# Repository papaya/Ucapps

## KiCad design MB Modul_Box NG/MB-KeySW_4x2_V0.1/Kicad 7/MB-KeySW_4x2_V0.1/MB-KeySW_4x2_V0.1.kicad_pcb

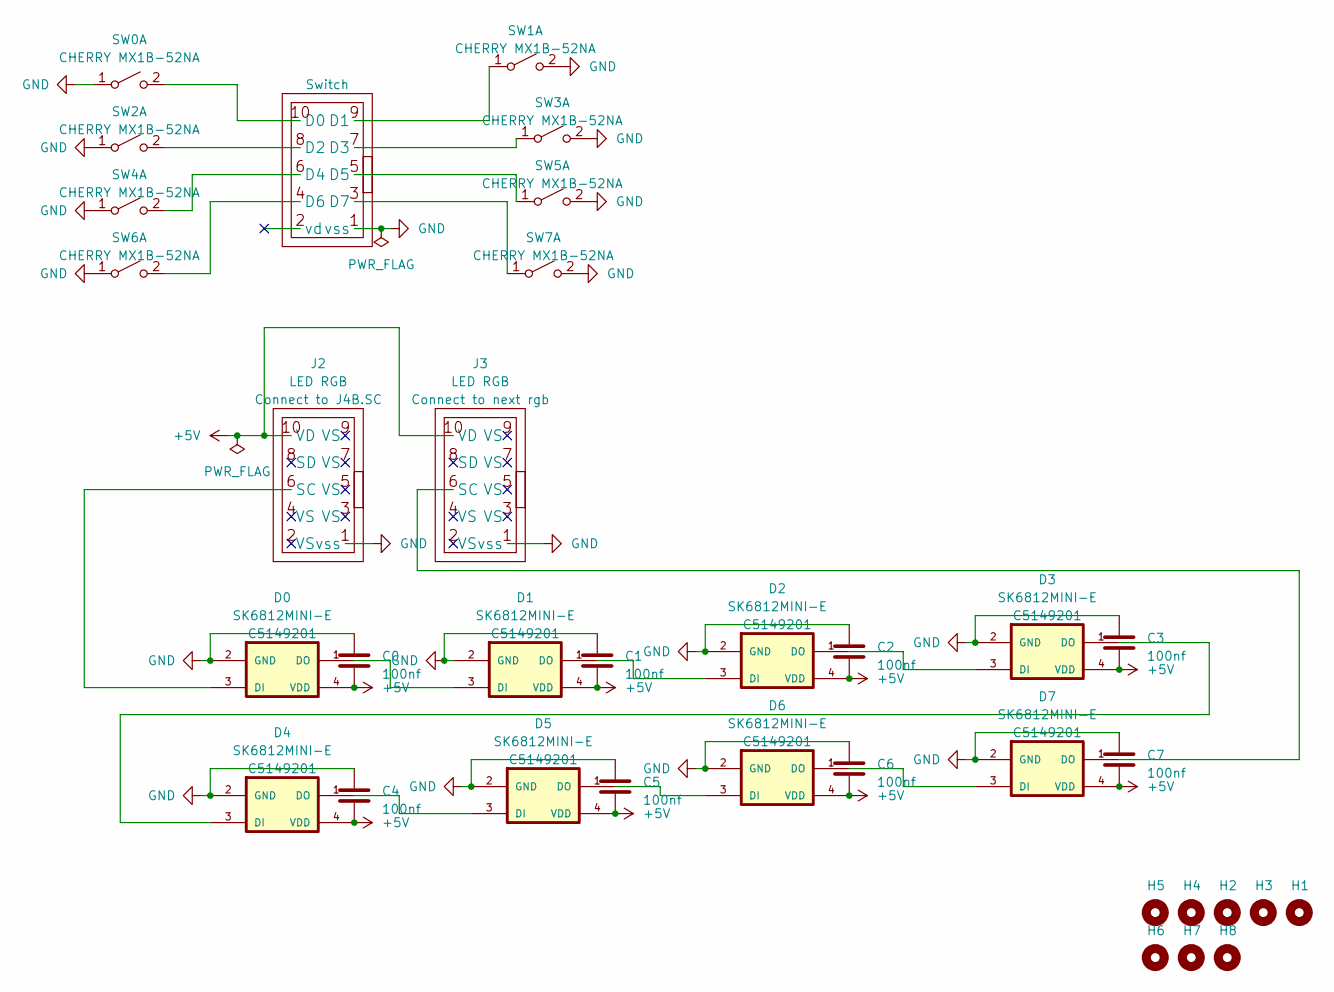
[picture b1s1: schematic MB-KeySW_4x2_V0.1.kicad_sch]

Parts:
C0: 100nf; C_0402_1005Metric; JLCPCB Part # C1525
C1, C2, C3, C4, C5, C6, C7: 100nf; CAPC1005X55N; JLCPCB Part # C1525
D0, D1, D2, D3, D4, D5, D6, D7: SK6812MINI-E; SK6812-MINI-E; JLCPCB Part # C5149201
H1, H2, H3, H4, H5, H6, H7, H8: MountingHole; MountingHole_3mm
J1, J2, J3: IDC-Header_2x05_P2.54mm_Vertical
SW0, SW1, SW2, SW3, SW4, SW5, SW6, SW7: CHERRY MX1B-52NA; SW_Alps_Matias_1.00u_cherry_LP

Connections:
+5V: C0.2, C1.2, C2.2, C3.2, C4.2, C5.2, C6.2, C7.2, D0.4 (VDD), D1.4 (VDD), D2.4 (VDD), D3.4 (VDD), D4.4 (VDD), D5.4 (VDD), D6.4 (VDD), D7.4 (VDD), J2.10 (VD), J3.10 (VD)
GND: C0.1, C1.1, C2.1, C3.1, C4.1, C5.1, C6.1, C7.1, D0.2 (GND), D1.2 (GND), D2.2 (GND), D3.2 (GND), D4.2 (GND), D5.2 (GND), D6.2 (GND), D7.2 (GND), J1.1 (vss), J2.1 (vss), J3.1 (vss), SW0.1 (A), SW1.2 (B), SW2.1 (A), SW3.2 (B), SW4.1 (A), SW5.2 (B), SW6.1 (A), SW7.2 (B)
unnamed: D0.3 (DI), J2.6 (SC)
unnamed: D0.1 (DO), D1.3 (DI)
unnamed: D1.1 (DO), D2.3 (DI)
unnamed: D2.1 (DO), D3.3 (DI)
unnamed: D3.1 (DO), D4.3 (DI)
unnamed: D4.1 (DO), D5.3 (DI)
unnamed: D5.1 (DO), D6.3 (DI)
unnamed: D6.1 (DO), D7.3 (DI)
unnamed: D7.1 (DO), J3.6 (SC)
unnamed: J1.10 (D0), SW0.2 (B)
unnamed: J1.9 (D1), SW1.1 (A)
unnamed: J1.8 (D2), SW2.2 (B)
unnamed: J1.7 (D3), SW3.1 (A)
unnamed: J1.6 (D4), SW4.2 (B)
unnamed: J1.5 (D5), SW5.1 (A)
unnamed: J1.4 (D6), SW6.2 (B)
unnamed: J1.3 (D7), SW7.1 (A)

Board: 2 copper layers, 35 parts (19 on the bottom side), 19 nets, no tracks yet.

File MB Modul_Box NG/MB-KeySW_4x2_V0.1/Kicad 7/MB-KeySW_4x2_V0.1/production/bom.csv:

Designator,Footprint,Quantity,Value,LCSC Part #
C0,0402,1,100nf,C1525
"C1, C2, C3, C4, C5, C6, C7",CAPC1005X55N,7,100nf,C1525
"D0, D1, D2, D3, D4, D5, D6, D7",SK6812-MINI-E,8,SK6812MINI-E,C5149201
"H11, H12, H13, H14",MountingHole_3mm,4,MountingHole,
"J1, J2, J3",IDC-Header_2x05_P2.54mm_Vertical,3,IDC-Header_2x05_P2.54mm_Vertical,
"SW0, SW1, SW2, SW3, SW4, SW5, SW6, SW7",Cherry-MX-Low-Profile,8,CHERRY MX1B-52NA,

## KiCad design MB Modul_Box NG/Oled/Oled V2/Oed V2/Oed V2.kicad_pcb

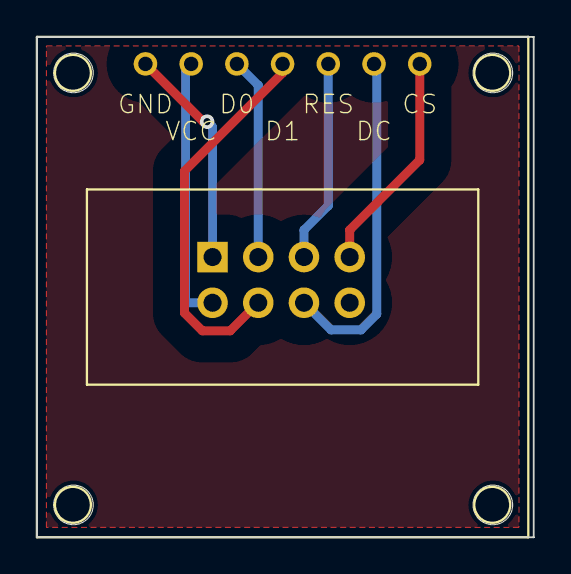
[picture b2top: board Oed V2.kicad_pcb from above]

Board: 2 copper layers, 27.6 x 27.8 mm, 6 parts (1 on the bottom side), 7 nets.

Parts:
H1, H3, H4: MountingHole; MountingHole_2.2mm_M2
J1: PinHeader_2x04_P2.54mm_Vertical
OLED1: OLED; oled-OLED_STANDARD
eeee1: MountingHole; MountingHole_2.2mm_M2

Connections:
+5V: J1.2, OLED1.VCC
CS1: J1.7, OLED1.CS
D01: J1.3, OLED1.D0
D11: J1.4, OLED1.D1
DC1: J1.6, OLED1.DC
GND: J1.1, OLED1.GND
RES1: J1.5, OLED1.RES

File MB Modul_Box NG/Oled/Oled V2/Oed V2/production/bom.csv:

Designator,Footprint,Quantity,Value,LCSC Part #
"H1, H3, H4, eeee1",MountingHole_2.2mm_M2,4,MountingHole,
J1,PinHeader_2x04_P2.54mm_Vertical,1,~,
OLED1,oled-OLED_STANDARD,1,OLED,

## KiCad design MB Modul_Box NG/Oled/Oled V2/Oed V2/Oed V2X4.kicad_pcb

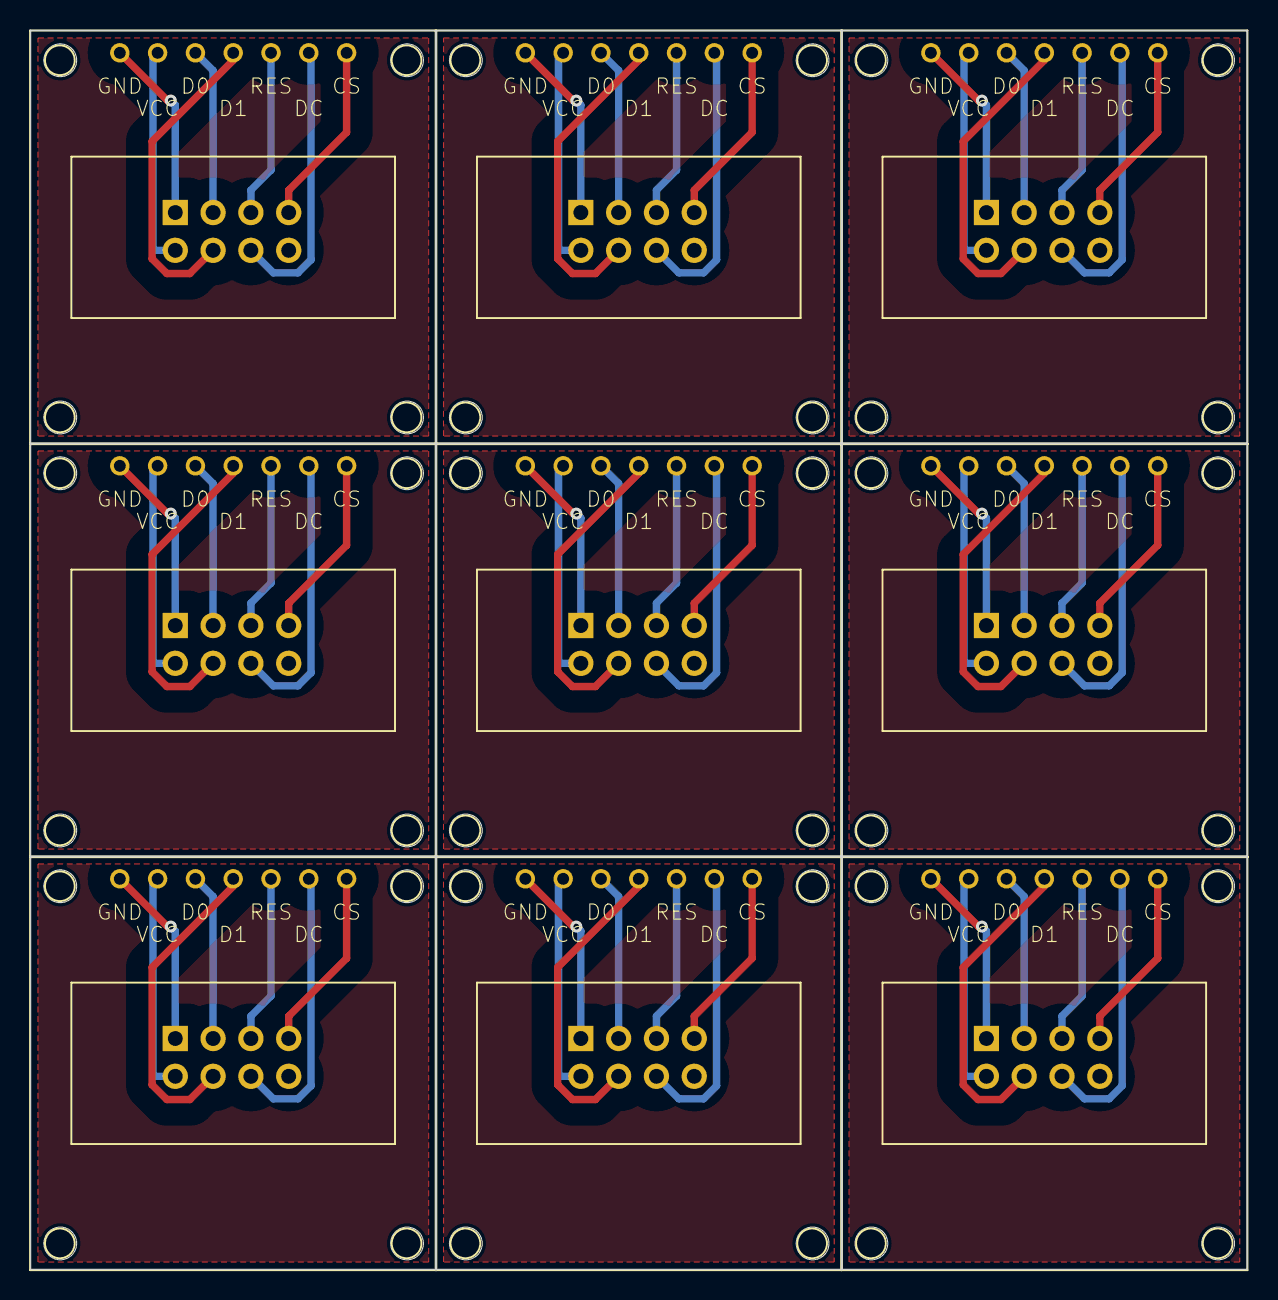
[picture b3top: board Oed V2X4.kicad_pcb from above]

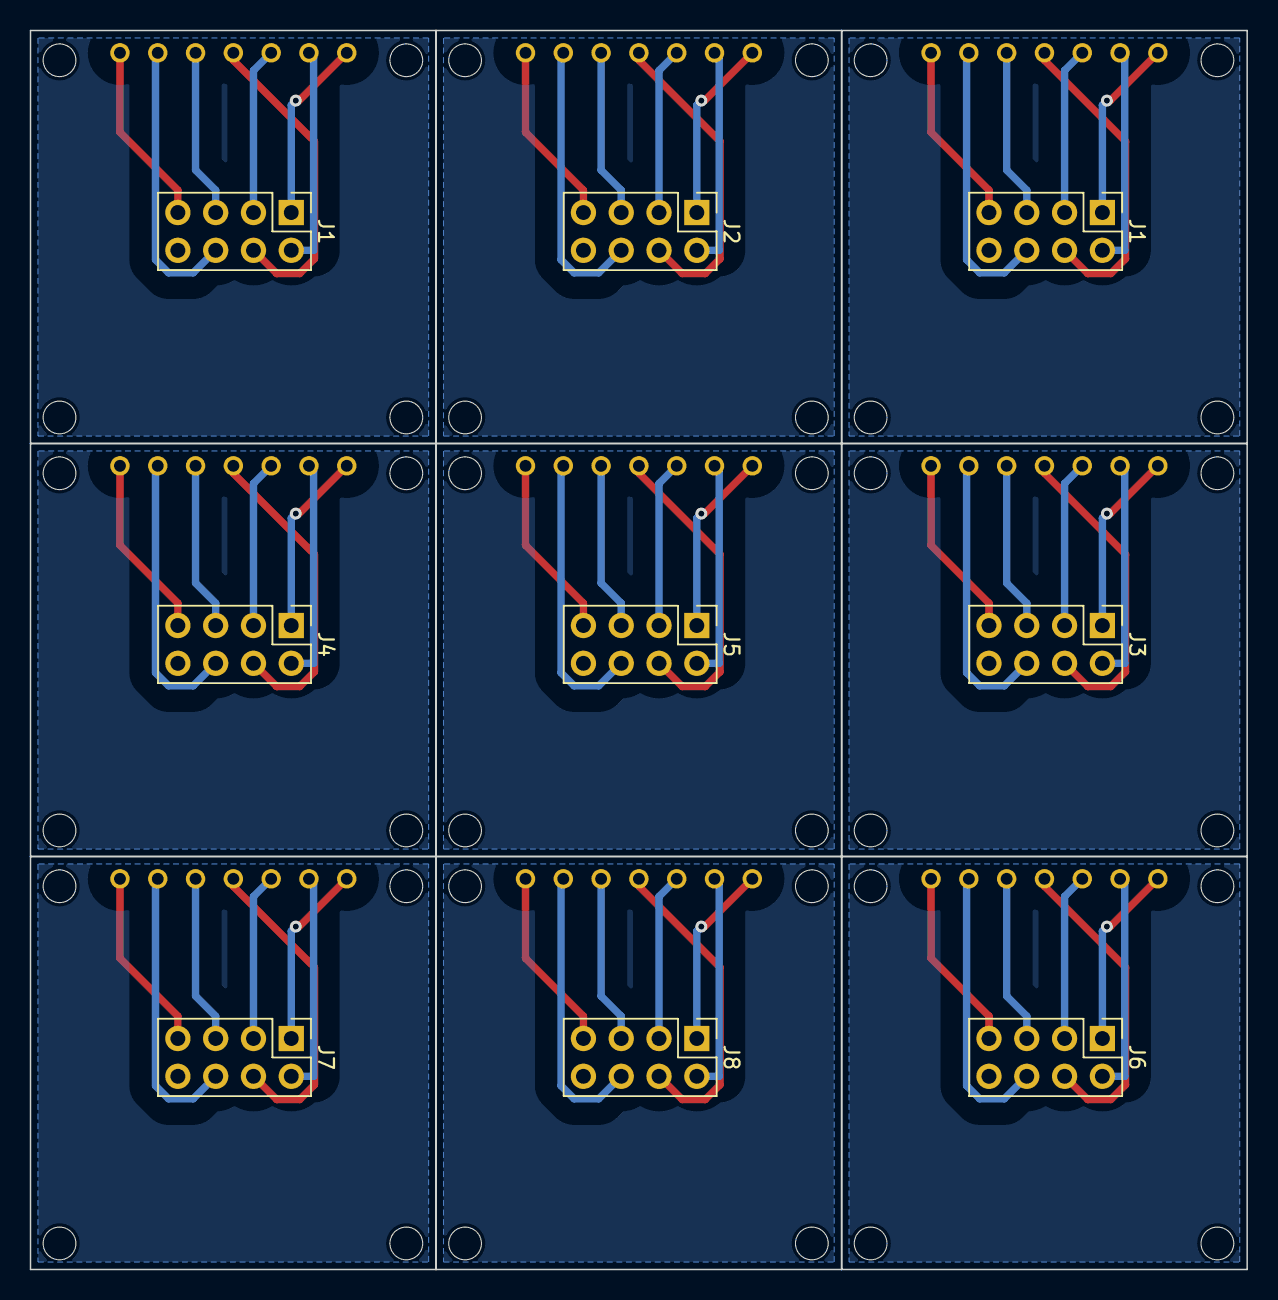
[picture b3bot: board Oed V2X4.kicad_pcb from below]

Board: 2 copper layers, 81.8 x 83.2 mm, 54 parts (9 on the bottom side), 7 nets.

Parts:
H1, H1#2, H2, H3, H3#2, H4, H4#2, H5, H6, H7, H8, H9, H10, H11, H12, H13, H14, H15, H16, H17, H18, H19, H20, H21, H22, H23, H24: MountingHole; MountingHole_2.2mm_M2
J1, J1#2, J2, J3, J4, J5, J6, J7, J8: PinHeader_2x04_P2.54mm_Vertical
OLED1, OLED1#2, OLED2, OLED3, OLED4, OLED5, OLED6, OLED7, OLED8: OLED; oled-OLED_STANDARD
eeee1, eeee1#2, eeee2, eeee3, eeee4, eeee5, eeee6, eeee7, eeee8: MountingHole; MountingHole_2.2mm_M2

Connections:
+5V: J1.2, J1#2.2, J2.2, J3.2, J4.2, J5.2, J6.2, J7.2, J8.2, OLED1.VCC, OLED1#2.VCC, OLED2.VCC, OLED3.VCC, OLED4.VCC, OLED5.VCC, OLED6.VCC, OLED7.VCC, OLED8.VCC
CS1: J1.7, J1#2.7, J2.7, J3.7, J4.7, J5.7, J6.7, J7.7, J8.7, OLED1.CS, OLED1#2.CS, OLED2.CS, OLED3.CS, OLED4.CS, OLED5.CS, OLED6.CS, OLED7.CS, OLED8.CS
D01: J1.3, J1#2.3, J2.3, J3.3, J4.3, J5.3, J6.3, J7.3, J8.3, OLED1.D0, OLED1#2.D0, OLED2.D0, OLED3.D0, OLED4.D0, OLED5.D0, OLED6.D0, OLED7.D0, OLED8.D0
D11: J1.4, J1#2.4, J2.4, J3.4, J4.4, J5.4, J6.4, J7.4, J8.4, OLED1.D1, OLED1#2.D1, OLED2.D1, OLED3.D1, OLED4.D1, OLED5.D1, OLED6.D1, OLED7.D1, OLED8.D1
DC1: J1.6, J1#2.6, J2.6, J3.6, J4.6, J5.6, J6.6, J7.6, J8.6, OLED1.DC, OLED1#2.DC, OLED2.DC, OLED3.DC, OLED4.DC, OLED5.DC, OLED6.DC, OLED7.DC, OLED8.DC
GND: J1.1, J1#2.1, J2.1, J3.1, J4.1, J5.1, J6.1, J7.1, J8.1, OLED1.GND, OLED1#2.GND, OLED2.GND, OLED3.GND, OLED4.GND, OLED5.GND, OLED6.GND, OLED7.GND, OLED8.GND
RES1: J1.5, J1#2.5, J2.5, J3.5, J4.5, J5.5, J6.5, J7.5, J8.5, OLED1.RES, OLED1#2.RES, OLED2.RES, OLED3.RES, OLED4.RES, OLED5.RES, OLED6.RES, OLED7.RES, OLED8.RES

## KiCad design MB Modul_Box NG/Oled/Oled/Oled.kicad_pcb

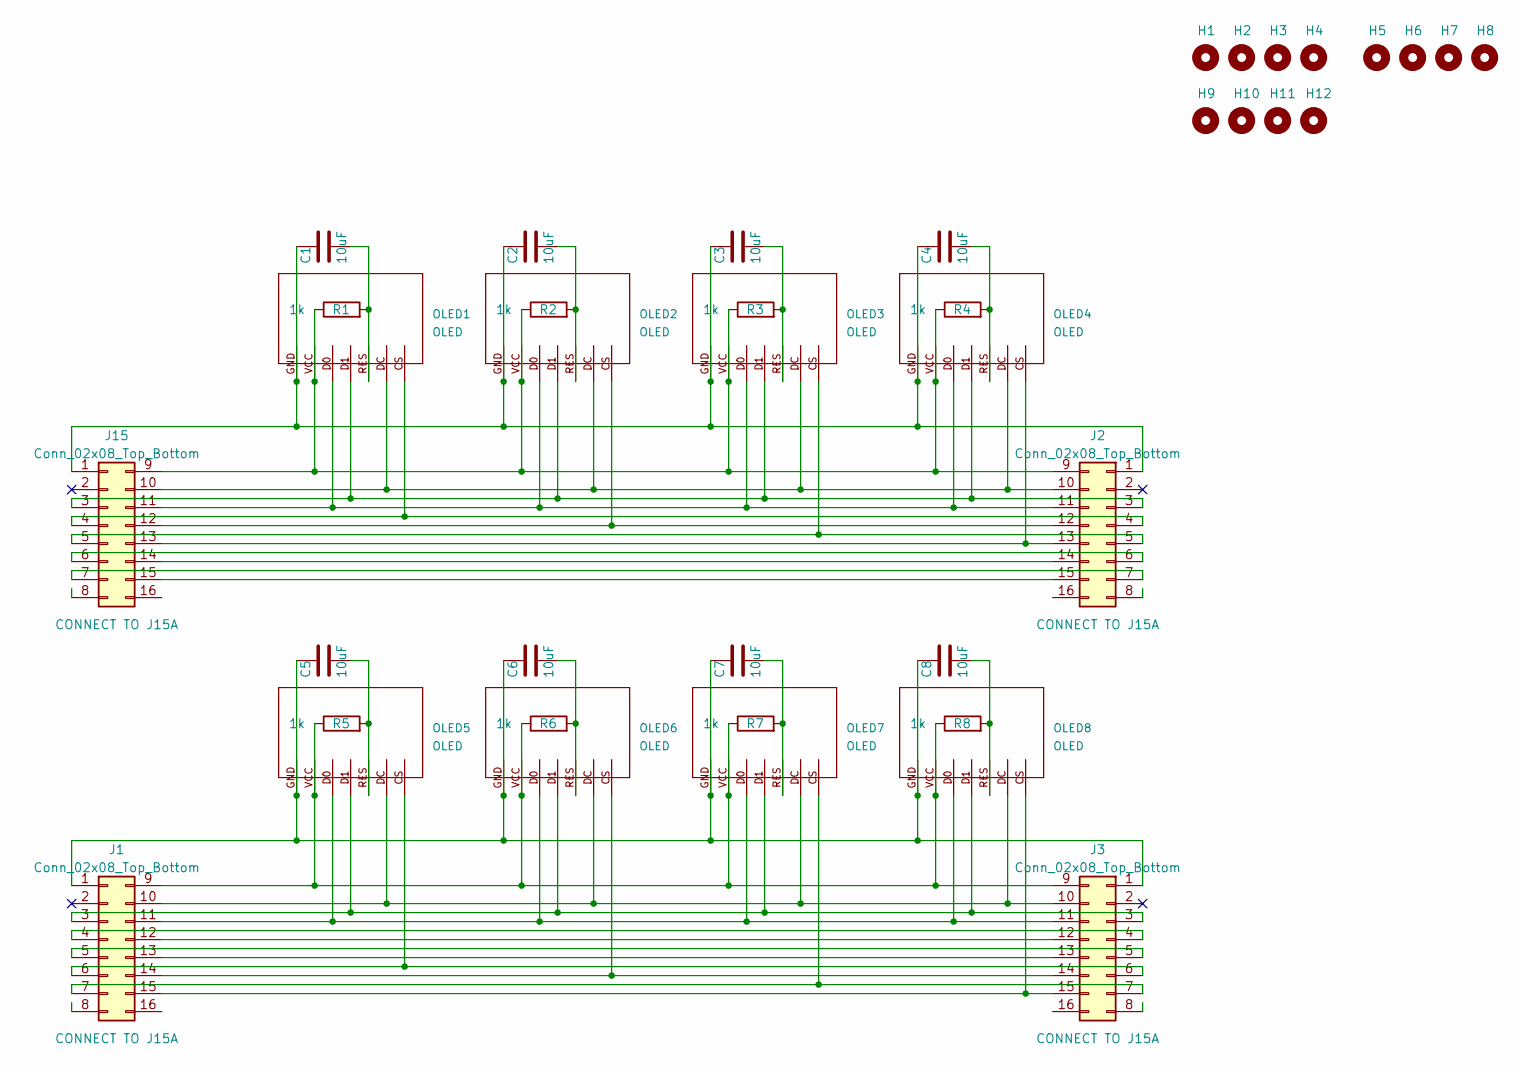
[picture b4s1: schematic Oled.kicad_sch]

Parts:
C1, C2, C3, C4, C5, C6, C7, C8: 10uF; C_Disc_D3.8mm_W2.6mm_P2.50mm
H1, H2, H3, H4, H5, H6, H7, H8, H9, H10, H11, H12: MountingHole; MountingHole_2.2mm_M2
J1, J2, J3, J15: Conn_02x08_Top_Bottom; PinHeader_2x08_P2.54mm_Vertical
OLED1, OLED2, OLED3, OLED4, OLED5, OLED6, OLED7, OLED8: OLED; oled-OLED_STANDARD
R1, R2, R3, R4, R5, R6, R7, R8: 1k; R_Axial_DIN0204_L3.6mm_D1.6mm_P5.08mm_Horizontal; JLCPCB Part # C1035

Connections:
unnamed: C1.1, OLED1.RES, R1.2
unnamed: C2.1, OLED2.RES, R2.2
unnamed: C3.1, OLED3.RES, R3.2
unnamed: C4.1, OLED4.RES, R4.2
unnamed: C5.1, OLED5.RES, R5.2
unnamed: C6.1, OLED6.RES, R6.2
unnamed: C7.1, OLED7.RES, R7.2
unnamed: C8.1, OLED8.RES, R8.2
unnamed: C5.2, C6.2, C7.2, C8.2, J1.1, J3.1, OLED5.GND, OLED6.GND, OLED7.GND, OLED8.GND
unnamed: J1.3, J3.3, OLED5.D1, OLED6.D1, OLED7.D1, OLED8.D1
unnamed: J1.4, J3.4
unnamed: J1.5, J3.5
unnamed: J1.6, J3.6, OLED5.CS
unnamed: J1.7, J3.7, OLED7.CS
unnamed: J1.9, J3.9, OLED5.VCC, OLED6.VCC, OLED7.VCC, OLED8.VCC, R5.1, R6.1, R7.1, R8.1
unnamed: J1.10, J3.10, OLED5.DC, OLED6.DC, OLED7.DC, OLED8.DC
unnamed: J1.11, J3.11, OLED5.D0, OLED6.D0, OLED7.D0, OLED8.D0
unnamed: J1.12, J3.12
unnamed: J1.13, J3.13
unnamed: J1.14, J3.14, OLED6.CS
unnamed: J1.15, J3.15, OLED8.CS
unnamed: C1.2, C2.2, C3.2, C4.2, J2.1, J15.1, OLED1.GND, OLED2.GND, OLED3.GND, OLED4.GND
unnamed: J2.3, J15.3, OLED1.D1, OLED2.D1, OLED3.D1, OLED4.D1
unnamed: J2.4, J15.4, OLED1.CS
unnamed: J2.5, J15.5, OLED3.CS
unnamed: J2.6, J15.6
unnamed: J2.7, J15.7
unnamed: J2.9, J15.9, OLED1.VCC, OLED2.VCC, OLED3.VCC, OLED4.VCC, R1.1, R2.1, R3.1, R4.1
unnamed: J2.10, J15.10, OLED1.DC, OLED2.DC, OLED3.DC, OLED4.DC
unnamed: J2.11, J15.11, OLED1.D0, OLED2.D0, OLED3.D0, OLED4.D0
unnamed: J2.12, J15.12, OLED2.CS
unnamed: J2.13, J15.13, OLED4.CS
unnamed: J2.14, J15.14
unnamed: J2.15, J15.15

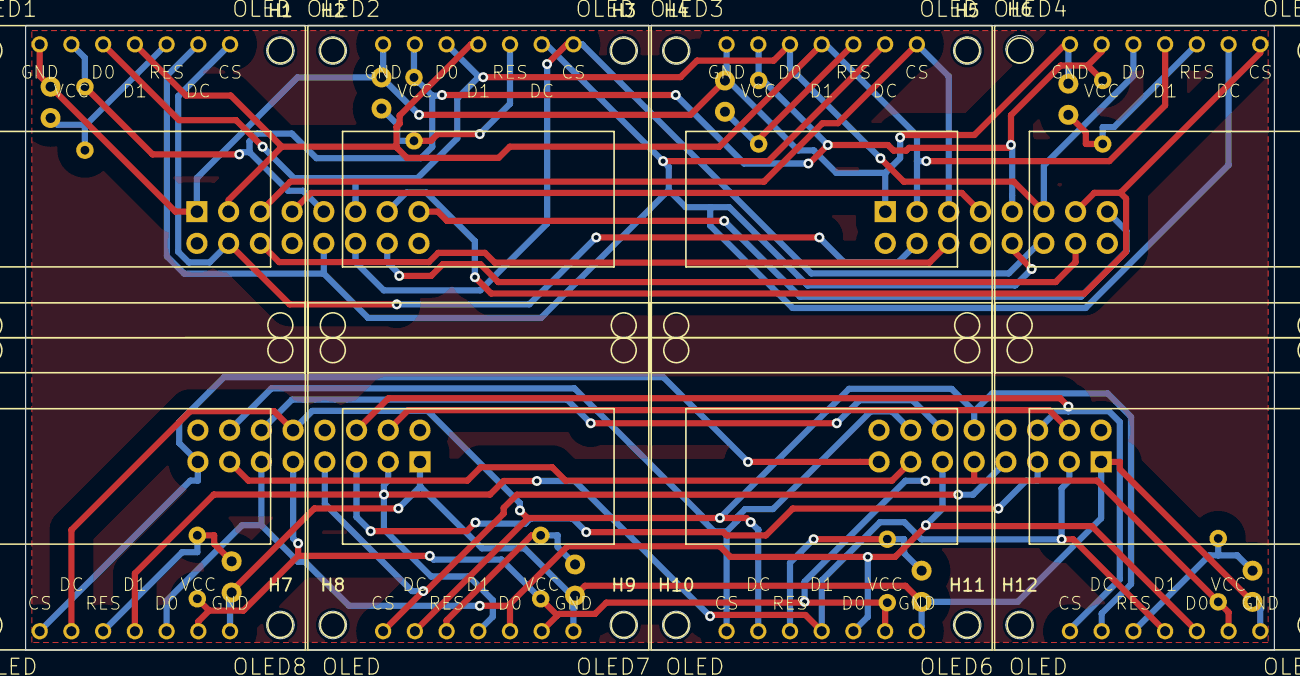
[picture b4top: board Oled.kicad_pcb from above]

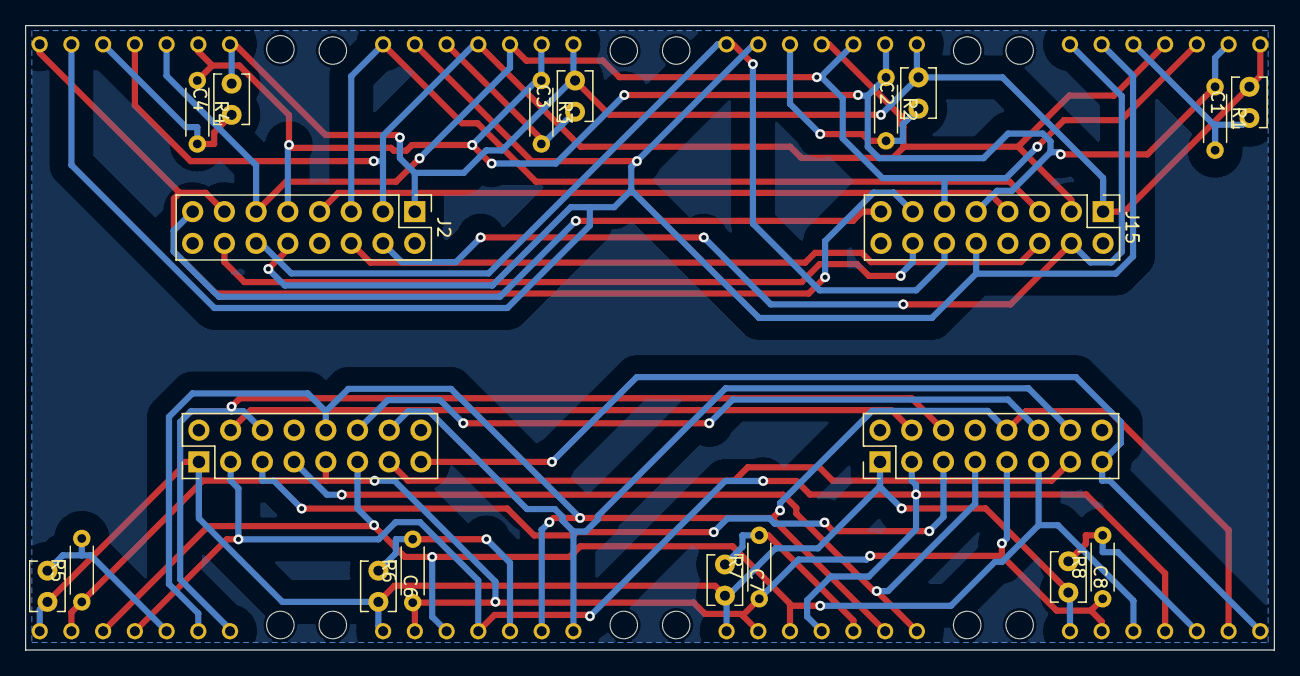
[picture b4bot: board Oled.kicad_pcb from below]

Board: 2 copper layers, 100.0 x 50.0 mm, 40 parts (20 on the bottom side), 34 nets.
